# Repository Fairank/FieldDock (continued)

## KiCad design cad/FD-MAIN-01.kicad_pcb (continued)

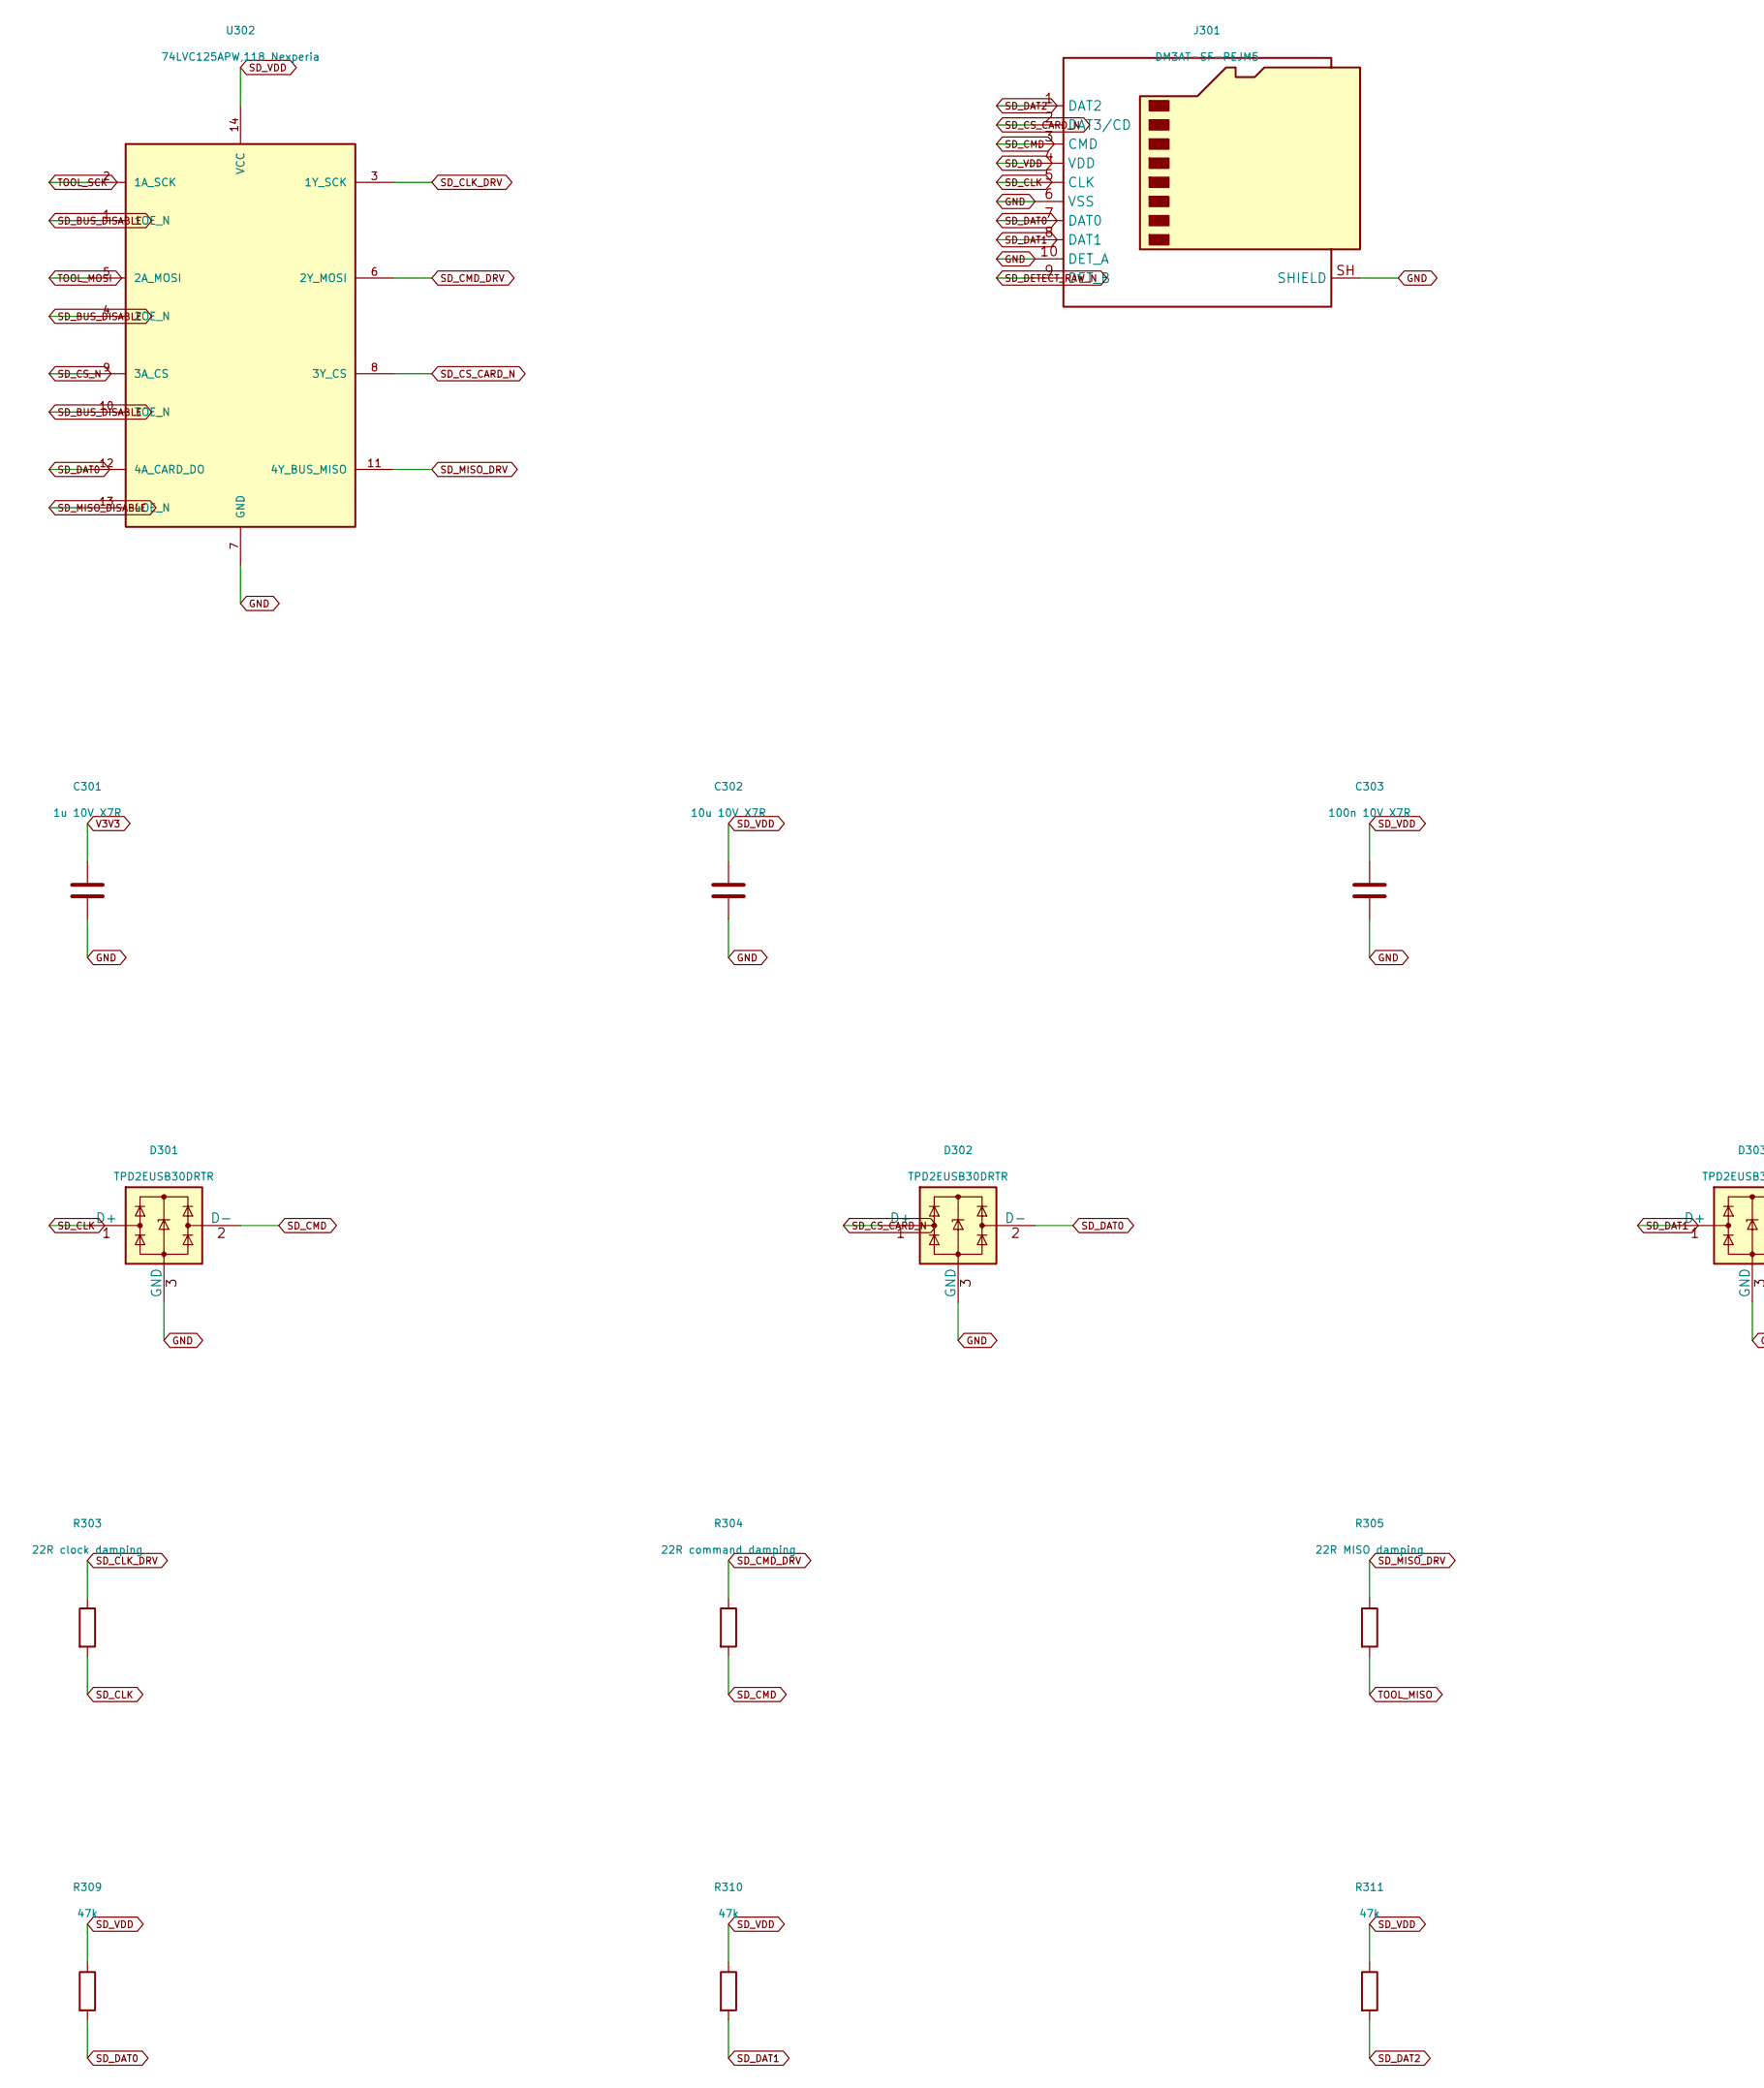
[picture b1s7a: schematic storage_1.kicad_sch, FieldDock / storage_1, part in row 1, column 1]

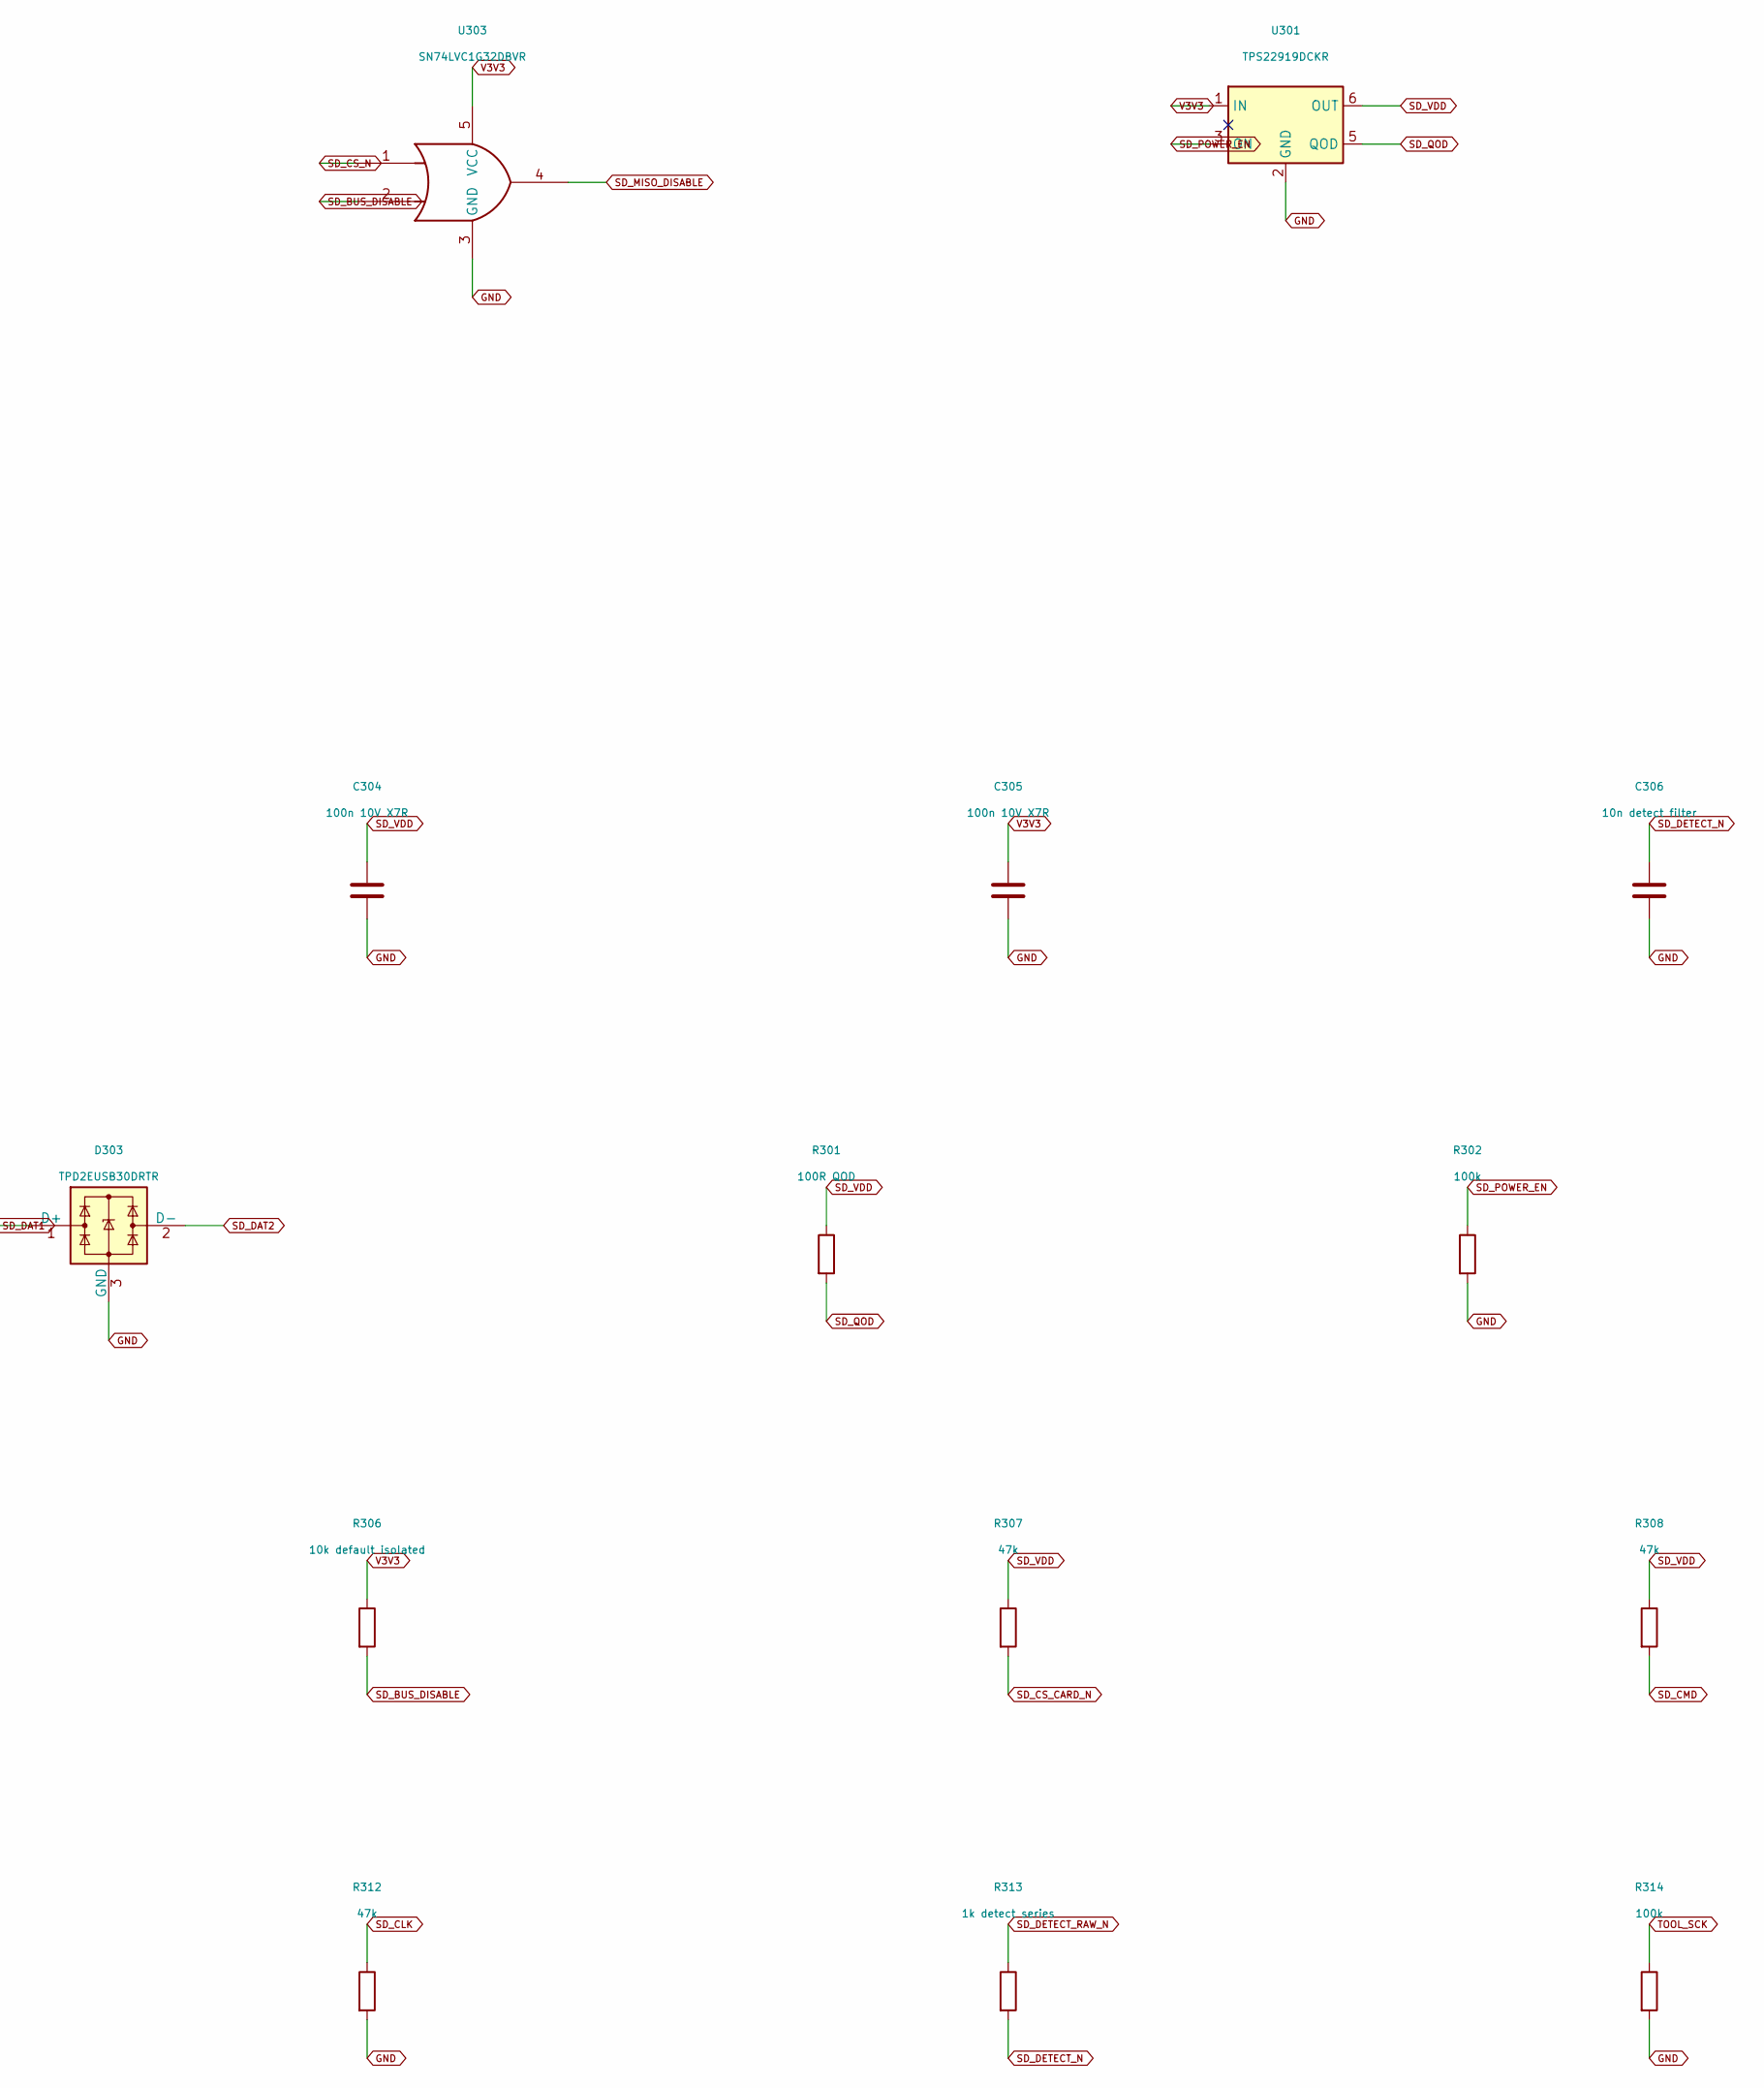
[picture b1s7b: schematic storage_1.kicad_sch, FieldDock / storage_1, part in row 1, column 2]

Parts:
C301: 1u 10V X7R; C_0603_1608Metric
C302: 10u 10V X7R; C_0805_2012Metric
C303, C304, C305: 100n 10V X7R; C_0603_1608Metric
C306: 10n detect filter; C_0603_1608Metric
D301, D302, D303: TPD2EUSB30DRTR; Texas_DRT-3
J301: DM3AT-SF-PEJM5; microSD_HC_Hirose_DM3AT-SF-PEJM5
R301: 100R QOD; R_0603_1608Metric
R302, R314: 100k; R_0603_1608Metric
R303: 22R clock damping; R_0603_1608Metric
R304: 22R command damping; R_0603_1608Metric
R305: 22R MISO damping; R_0603_1608Metric
R306: 10k default isolated; R_0603_1608Metric
R307, R308, R309, R310, R311, R312: 47k; R_0603_1608Metric
R313: 1k detect series; R_0603_1608Metric
U301: TPS22919DCKR; SOT-363_SC-70-6
U302: 74LVC125APW,118 Nexperia; TSSOP-14_4.4x5mm_P0.65mm
U303: SN74LVC1G32DBVR; SOT-23-5

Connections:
GND: C301.2, C302.2, C303.2, C304.2, C305.2, C306.2, D301.3 (GND), D302.3 (GND), D303.3 (GND), J301.6 (VSS), J301.10 (DET_A), J301.SH (SHIELD), R302.2, R312.2, R314.2, U301.2 (GND), U302.7 (GND), U303.3 (GND); also elsewhere on the board
SD_BUS_DISABLE: R306.2, U302.1 (1OE_N), U302.4 (2OE_N), U302.10 (3OE_N), U303.2; also elsewhere on the board
SD_CLK: D301.1 (D+), J301.5 (CLK), R303.2, R312.1
SD_CLK_DRV: R303.1, U302.3 (1Y_SCK)
SD_CMD: D301.2 (D-), J301.3 (CMD), R304.2, R308.2
SD_CMD_DRV: R304.1, U302.6 (2Y_MOSI)
SD_CS_CARD_N: D302.1 (D+), J301.2 (DAT3/CD), R307.2, U302.8 (3Y_CS)
SD_CS_N: U302.9 (3A_CS), U303.1; also elsewhere on the board
SD_DAT0: D302.2 (D-), J301.7 (DAT0), R309.2, U302.12 (4A_CARD_DO)
SD_DAT1: D303.1 (D+), J301.8 (DAT1), R310.2
SD_DAT2: D303.2 (D-), J301.1 (DAT2), R311.2
SD_DETECT_N: C306.1, R313.2; also elsewhere on the board
SD_DETECT_RAW_N: J301.9 (DET_B), R313.1
SD_MISO_DISABLE: U302.13 (4OE_N), U303.4; also elsewhere on the board
SD_MISO_DRV: R305.1, U302.11 (4Y_BUS_MISO)
SD_POWER_EN: R302.1, U301.3 (ON); also elsewhere on the board
SD_QOD: R301.2, U301.5 (QOD)
SD_VDD: C302.1, C303.1, C304.1, J301.4 (VDD), R301.1, R307.1, R308.1, R309.1, R310.1, R311.1, U301.6 (OUT), U302.14 (VCC)
TOOL_MISO: R305.2; also elsewhere on the board
TOOL_MOSI: U302.5 (2A_MOSI); also elsewhere on the board
TOOL_SCK: R314.1, U302.2 (1A_SCK); also elsewhere on the board
V3V3: C301.1, C305.1, R306.1, U301.1 (IN), U303.5 (VCC); also elsewhere on the board

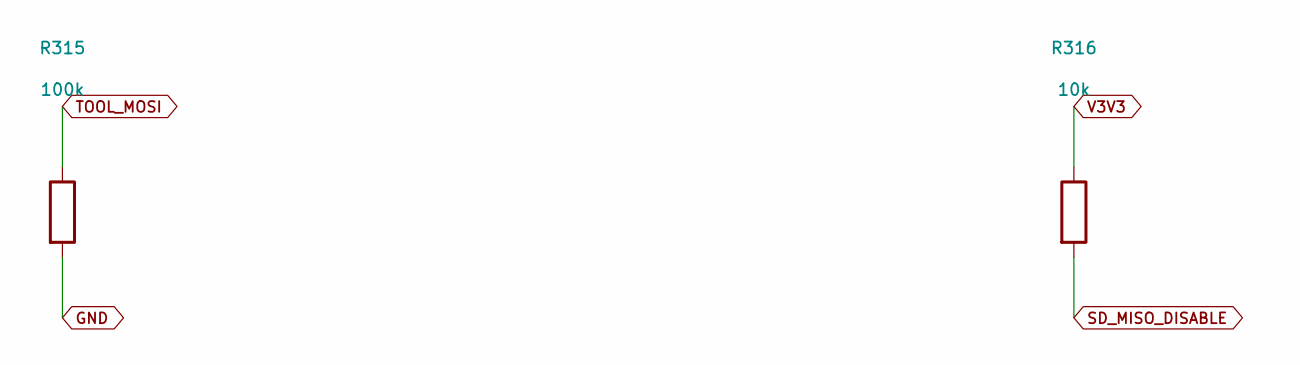
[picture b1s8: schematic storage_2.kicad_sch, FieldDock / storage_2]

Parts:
R315: 100k; R_0603_1608Metric
R316: 10k; R_0603_1608Metric

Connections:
GND: R315.2; also elsewhere on the board
SD_MISO_DISABLE: R316.2; also elsewhere on the board
TOOL_MOSI: R315.1; also elsewhere on the board
V3V3: R316.1; also elsewhere on the board

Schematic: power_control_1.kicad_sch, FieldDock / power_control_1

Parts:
C180: 1u 10V X7R; C_0603_1608Metric
C181: 10u 10V X7R; C_0805_2012Metric
C190, C194: 1n 50V C0G; C_0603_1608Metric
C191, C192, C195, C196, C197: 100n 10V X7R; C_0603_1608Metric
R180: 34.0k 1%; R_0402_1005Metric
R181, R197, R198, R199: 100k 1%; R_0402_1005Metric
R182: 1k 1%; R_0402_1005Metric
R190, R194: 324k 1%; R_0402_1005Metric
R191, R195: 33.2k 1%; R_0402_1005Metric
R192, R193, R196: 10k 1%; R_0402_1005Metric
U190: TPS3700DDCR; SOT-23-6
U191: SN74LVC1G04DBVR; SOT-23-5
U192, U193, U194: SN74LVC1G08DBVR; SOT-23-5
U195: TPS2553DBVR; SOT-23-6

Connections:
AUX_5V_PROTECTED: C180.1, U195.1 (IN); also elsewhere on the board
AUX_PROBE_ALLOWED: U192.4, U194.1
AUX_PROBE_BUDGET_OK: R197.1, U192.2; also elsewhere on the board
AUX_VBUS_RAW: R194.1; also elsewhere on the board
AUX_VGOOD_N: R193.2, U190.6 (OUTB), U191.2
AUX_VSENSE: C194.1, R194.2, R195.1, U190.4 (INB_N)
EXT_FAULT_N: R181.2, U195.4 (FAULT_N)
EXT_GOOD: U191.4, U192.1; also elsewhere on the board
EXT_ILIM: R180.1, U195.5 (ILIM)
EXT_LOAD_ENABLE: R199.1, U194.4, U195.3 (EN); also elsewhere on the board
EXT_PROBE5: C181.1, R182.1, U195.6 (OUT); also elsewhere on the board
EXT_REQUEST: R198.1, U193.2; also elsewhere on the board
GND: C180.2, C181.2, C190.2, C191.2, C192.2, C194.2, C195.2, C196.2, C197.2, R180.2, R182.2, R191.2, R195.2, R197.2, R198.2, R199.2, U190.2 (GND), U191.3 (GND), U192.3 (GND), U193.3 (GND), U194.3 (GND), U195.2 (GND); also elsewhere on the board
MGMT_IRQ_N: R196.2; also elsewhere on the board
PHONE_ATTACHED: R192.2, U190.1 (OUTA); also elsewhere on the board
PHONE_VBUS_RAW: R190.1; also elsewhere on the board
PHONE_VSENSE: C190.1, R190.2, R191.1, U190.3 (INA_P)
PROBE_REQUEST_ALLOWED: U193.4, U194.2
TOOLS_ENABLE: U193.1; also elsewhere on the board
V3V3: C191.1, C192.1, C195.1, C196.1, C197.1, R181.1, R192.1, R193.1, R196.1, U190.5 (VDD), U191.5 (VCC), U192.5 (VCC), U193.5 (VCC), U194.5 (VCC); also elsewhere on the board

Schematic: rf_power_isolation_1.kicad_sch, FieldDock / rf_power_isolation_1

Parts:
C400: 1u 10V X7R; C_0603_1608Metric
C401: 4.7u 10V X7R; C_0603_1608Metric
C402, C403, C404: 100n 10V X7R; C_0402_1005Metric
R400: 100R; R_0402_1005Metric
R401, R403, R406, R407, R408, R409, R410: 100k; R_0402_1005Metric
R402: 10k; R_0402_1005Metric
R404, R405: 47k; R_0402_1005Metric
U400: TPS22919DCKR; SOT-363_SC-70-6
U401: SN74LVC1G08DBVR; SOT-23-5
U402: SN74LVC1G04DBVR; SOT-23-5
U403: SN74CB3T3245PWR; TSSOP-20_4.4x6.5mm_P0.65mm

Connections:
GND: C400.2, C401.2, C402.2, C403.2, C404.2, R401.2, R403.2, R406.2, R407.2, R408.2, R409.2, R410.2, U400.2 (GND), U401.3 (GND), U402.3 (GND), U403.10 (GND); also elsewhere on the board
NFC_CS_N: U403.6 (A5); also elsewhere on the board
NFC_IRQ: R409.1, U403.8 (A7); also elsewhere on the board
RF_NFC_CS_N: R405.2, U403.14 (B5); also elsewhere on the board
RF_NFC_IRQ: U403.12 (B7); also elsewhere on the board
RF_QOD: R400.2, U400.5 (QOD)
RF_SUB_CS_N: R404.2, U403.15 (B4); also elsewhere on the board
RF_SUB_GDO0: U403.13 (B6); also elsewhere on the board
RF_SUB_RF_SELECT: R408.1, U403.11 (B8); also elsewhere on the board
RF_TOOL_MISO: U403.16 (B3); also elsewhere on the board
RF_TOOL_MOSI: R407.1, U403.17 (B2); also elsewhere on the board
RF_TOOL_SCK: R406.1, U403.18 (B1); also elsewhere on the board
SUB_CS_N: U403.5 (A4); also elsewhere on the board
SUB_GDO0: R410.1, U403.7 (A6); also elsewhere on the board
SUB_RF_SELECT: U403.9 (A8); also elsewhere on the board
TOOLS_BUS_DISABLE: R402.2, U402.4, U403.19 (OE_N); also elsewhere on the board
TOOLS_ENABLE: U400.3 (ON), U401.1; also elsewhere on the board
TOOLS_IO_ARM: R401.1, U401.2; also elsewhere on the board
TOOLS_IO_ENABLED: R403.1, U401.4, U402.2; also elsewhere on the board
TOOL_MISO: U403.4 (A3); also elsewhere on the board
TOOL_MOSI: U403.3 (A2); also elsewhere on the board
TOOL_SCK: U403.2 (A1); also elsewhere on the board
V3V3: C400.1, C402.1, C403.1, C404.1, R402.1, U400.1 (IN), U401.5 (VCC), U402.5 (VCC), U403.20 (VCC); also elsewhere on the board
V3V3_RF: C401.1, R400.1, R404.1, R405.1, U400.6 (OUT); also elsewhere on the board

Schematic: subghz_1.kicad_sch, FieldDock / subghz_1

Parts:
C430, C431: 9p C0G 50V initial CL trim; C_0402_1005Metric
C432, C433, C434, C435, C436, C437, C438: 100n 10V X7R; C_0402_1005Metric
C439: 2.2u 10V X7R; C_0603_1608Metric
C440, C441: 100p C0G 50V; C_0402_1005Metric
C442: 1.2p C0G 0.1p 50V; C_0402_1005Metric
C443, C444, C445: DNP C0G matching trim; C_0402_1005Metric
C446, C447: 10n 10V X7R; C_0402_1005Metric
C450, C451: 12p C0G 2% 50V; C_0402_1005Metric
C452, C453: 8.2p C0G 2% 50V; C_0402_1005Metric
C454, C455: 4.3p C0G 2% 50V; C_0402_1005Metric
J430: U.FL-R-SMT-1(10) / 50R antenna; U.FL_Hirose_U.FL-R-SMT-1_Vertical
U430: CC1101RGPT; Texas_RGP0020H_VQFN-20-1EP_4x4mm_P0.5mm_EP2.4x2.4mm
U431, U432: BGS13S4N9E6327XTSA1; Infineon_TSNP9_1.1x1.1_P0.4

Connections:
GND: C430.2, C431.2, C432.2, C433.2, C434.2, C435.2, C436.2, C437.2, C438.2, C439.2, C442.2, C443.2, C444.2, C445.2, C446.2, C447.2, C450.2, C451.2, C452.2, C453.2, C454.2, C455.2, J430.2 (Ext), U430.16 (GND1), U430.18 (DGUARD), U430.19 (GND2), U430.21 (EP_GND), U431.6 (DGND), U431.9 (GND), U432.6 (DGND), U432.9 (GND); also elsewhere on the board
RF_SUB_CS_N: U430.7 (CS_N); also elsewhere on the board
RF_SUB_GDO0: U430.6 (GDO0); also elsewhere on the board
RF_SUB_RF_SELECT: U431.1 (V1), U432.1 (V1); also elsewhere on the board
RF_TOOL_MISO: U430.2 (SO_GDO1); also elsewhere on the board
RF_TOOL_MOSI: U430.20 (SI); also elsewhere on the board
RF_TOOL_SCK: U430.1 (SCLK); also elsewhere on the board
SUB_ANT: J430.1 (In); also elsewhere on the board
SUB_BAL_A: C440.2; also elsewhere on the board
SUB_BAL_B: C441.2; also elsewhere on the board
SUB_DCOUPL: C432.1, U430.5 (DCOUPL)
SUB_FILTER_IN: C445.1, U431.4 (RFIN); also elsewhere on the board
SUB_FILTER_OUT: U432.4 (RFIN); also elsewhere on the board
SUB_F_IN_315: U431.3 (RF1); also elsewhere on the board
SUB_F_IN_433: U431.5 (RF2); also elsewhere on the board
SUB_F_IN_900: U431.2 (RF3); also elsewhere on the board
SUB_F_M1_315: C450.1; also elsewhere on the board
SUB_F_M1_433: C452.1; also elsewhere on the board
SUB_F_M1_900: C454.1; also elsewhere on the board
SUB_F_M2_315: C451.1; also elsewhere on the board
SUB_F_M2_433: C453.1; also elsewhere on the board
SUB_F_M2_900: C455.1; also elsewhere on the board
SUB_F_OUT_315: U432.3 (RF1); also elsewhere on the board
SUB_F_OUT_433: U432.5 (RF2); also elsewhere on the board
SUB_F_OUT_900: U432.2 (RF3); also elsewhere on the board
SUB_MATCH: C442.1; also elsewhere on the board
SUB_RBIAS: U430.17 (RBIAS); also elsewhere on the board
SUB_RFN: C440.1, C444.1, U430.13 (RF_N)
SUB_RFP: C441.1, C443.1, U430.12 (RF_P)
SUB_SWITCH_V2: U430.3 (GDO2), U431.8 (V2), U432.8 (V2); also elsewhere on the board
SUB_X1: C430.1, U430.8 (XOSC_Q1); also elsewhere on the board
SUB_X2: C431.1, U430.10 (XOSC_Q2); also elsewhere on the board
V3V3_RF: C433.1, C434.1, C435.1, C436.1, C437.1, C438.1, C439.1, C446.1, C447.1, U430.4 (DVDD), U430.9 (AVDD1), U430.11 (AVDD2), U430.14 (AVDD3), U430.15 (AVDD4), U431.7 (VDD), U432.7 (VDD); also elsewhere on the board

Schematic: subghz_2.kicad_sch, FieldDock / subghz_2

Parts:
L430: 3.3nH 0.2nH RF; L_0402_1005Metric
L431: 6.8nH 0.2nH RF; L_0402_1005Metric
L440, L442: 12nH 5% RF; L_0402_1005Metric
L441: 39nH 5% RF; L_0402_1005Metric
L443, L445: 8.2nH 5% RF; L_0402_1005Metric
L444: 27nH 5% RF; L_0402_1005Metric
L446, L448: 4.3nH 5% RF; L_0402_1005Metric
L447: 13nH 5% RF; L_0402_1005Metric
R430: 56k 1%; R_0402_1005Metric
R431: 100k; R_0402_1005Metric
R432: 0R antenna matching link; R_0402_1005Metric
T430: B0310J50100AHF; TTM_B0310J50100AHF
Y430: XRCGB26M000F3M00R0 26MHz CL6pF; Murata_XRCGB_2016

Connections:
GND: R430.2, R431.2, T430.2 (GND); also elsewhere on the board
SUB_ANT: R432.2; also elsewhere on the board
SUB_BAL_A: T430.3 (BAL_100R_A); also elsewhere on the board
SUB_BAL_B: T430.4 (BAL_100R_B); also elsewhere on the board
SUB_FILTER_IN: L431.2; also elsewhere on the board
SUB_FILTER_OUT: R432.1; also elsewhere on the board
SUB_F_IN_315: L440.1; also elsewhere on the board
SUB_F_IN_433: L443.1; also elsewhere on the board
SUB_F_IN_900: L446.1; also elsewhere on the board
SUB_F_M1_315: L440.2, L441.1; also elsewhere on the board
SUB_F_M1_433: L443.2, L444.1; also elsewhere on the board
SUB_F_M1_900: L446.2, L447.1; also elsewhere on the board
SUB_F_M2_315: L441.2, L442.1; also elsewhere on the board
SUB_F_M2_433: L444.2, L445.1; also elsewhere on the board
SUB_F_M2_900: L447.2, L448.1; also elsewhere on the board
SUB_F_OUT_315: L442.2; also elsewhere on the board
SUB_F_OUT_433: L445.2; also elsewhere on the board
SUB_F_OUT_900: L448.2; also elsewhere on the board
SUB_MATCH: L430.2, L431.1; also elsewhere on the board
SUB_RBIAS: R430.1; also elsewhere on the board
SUB_SWITCH_V2: R431.1; also elsewhere on the board
SUB_UNBAL: L430.1, T430.1 (UNBAL_50R)
SUB_X1: Y430.1 (XTAL_1); also elsewhere on the board
SUB_X2: Y430.3 (XTAL_3); also elsewhere on the board

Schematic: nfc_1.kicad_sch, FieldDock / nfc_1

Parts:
C500, C501: 6p C0G 50V; C_0402_1005Metric
C502, C504, C506, C508, C510, C513: 10n 10V X7R; C_0402_1005Metric
C503, C505, C507, C509, C511: 2.2u 10V X7R; C_0603_1608Metric
C512: 1u 10V X7R; C_0603_1608Metric
C520, C525: 680p C0G 50V; C_0603_1608Metric
C521, C526: 100p C0G 100V; C_0603_1608Metric
C522, C527: 62p C0G 100V; C_0603_1608Metric
C523, C528: 10p C0G 100V; C_0603_1608Metric
C524, C529: 100p C0G 50V; C_0603_1608Metric
C530, C531: DNP C0G trim; C_0603_1608Metric
J500: NFC antenna 1.37uH nominal / soldered twisted pair; Antenna_2Pad_2mm
L500: 270nH 5% RF wirewound; L_0603_1608Metric
U500: ST25R3916-AQWT; ST_VFQFPN32_5x5_EP3.5

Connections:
GND: C500.2, C501.2, C502.2, C503.2, C504.2, C505.2, C506.2, C507.2, C508.2, C509.2, C510.2, C511.2, C512.2, C513.2, C520.2, C522.2, C524.2, C525.2, C527.2, C529.2, U500.6 (GND_D), U500.12 (GND_DR1), U500.16 (GND_DR2), U500.20 (I2C_EN), U500.21 (VSS), U500.26 (GND_A), U500.33 (EP_GND); also elsewhere on the board
NFC_AGDC: C512.1, C513.1, U500.24 (AGDC)
NFC_ANT_N: C526.2, C527.1, C528.1, C531.2; also elsewhere on the board
NFC_ANT_P: C521.2, C522.1, C523.1, C530.2; also elsewhere on the board
NFC_COIL_N: J500.2; also elsewhere on the board
NFC_COIL_P: J500.1; also elsewhere on the board
NFC_FILTER_N: C525.1, C526.1, C531.1; also elsewhere on the board
NFC_FILTER_P: C520.1, C521.1, C530.1, L500.2
NFC_RFI1: C523.2, C524.1, U500.22 (RFI1)
NFC_RFI2: C528.2, C529.1, U500.23 (RFI2)
NFC_RFO1: L500.1, U500.13 (RFO1)
NFC_RFO2: U500.15 (RFO2); also elsewhere on the board
NFC_VDD_A: C506.1, C507.1, U500.7 (VDD_A)
NFC_VDD_AM: C510.1, C511.1, U500.11 (VDD_AM)
NFC_VDD_D: C504.1, C505.1, U500.3 (VDD_D)
NFC_VDD_RF: C508.1, C509.1, U500.9 (VDD_RF), U500.14 (VDD_DR)
NFC_XTI: C501.1, U500.5 (XTI); also elsewhere on the board
NFC_XTO: C500.1, U500.4 (XTO); also elsewhere on the board
RF_NFC_CS_N: U500.29 (BSS_N); also elsewhere on the board
RF_NFC_IRQ: U500.27 (IRQ); also elsewhere on the board
RF_TOOL_MISO: U500.32 (MISO); also elsewhere on the board
RF_TOOL_MOSI: U500.31 (MOSI); also elsewhere on the board
RF_TOOL_SCK: U500.30 (SCLK); also elsewhere on the board
V3V3_RF: C502.1, C503.1, U500.1 (VDD_IO), U500.8 (VDD), U500.10 (VDD_TX); also elsewhere on the board

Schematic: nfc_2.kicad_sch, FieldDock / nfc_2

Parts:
L501: 270nH 5% RF wirewound; L_0603_1608Metric
R500, R501: 0R antenna tuning link; R_0603_1608Metric
Y500: XRCGB27M120F3M00R0 27.12MHz CL6pF; Murata_XRCGB_2016

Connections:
NFC_ANT_N: R501.1; also elsewhere on the board
NFC_ANT_P: R500.1; also elsewhere on the board
NFC_COIL_N: R501.2; also elsewhere on the board
NFC_COIL_P: R500.2; also elsewhere on the board
NFC_FILTER_N: L501.2; also elsewhere on the board
NFC_RFO2: L501.1; also elsewhere on the board
NFC_XTI: Y500.3 (XTAL_3); also elsewhere on the board
NFC_XTO: Y500.1 (XTAL_1); also elsewhere on the board

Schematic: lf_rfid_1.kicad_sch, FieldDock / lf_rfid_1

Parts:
C600, C610, C611: 1u 10V X7R; C_0603_1608Metric
C601: 4.7u 10V X7R; C_0603_1608Metric
C602, C603, C609, C612, C613, C625: 100n 10V X7R; C_0402_1005Metric
C604: 3.3n C0G 100V; C_0805_2012Metric
C605: DNP C0G 100V trim; C_0805_2012Metric
C606: 10n X7R 100V; C_0603_1608Metric
C607: 1n C0G 100V; C_0603_1608Metric
C608: 220n X7R 100V; C_0805_2012Metric
C620, C622: 4.7n C0G 50V; C_0402_1005Metric
C621, C623, C624: 100p C0G 50V; C_0402_1005Metric
D600: 1N4148W-7-F; D_SOD-123
D601: MM3Z33VT1G 33V; D_SOD-323
D602: BAT54S,215; SOT-23
J600: LF coil ~500uH / soldered twisted pair; Antenna_2Pad_2mm
U600, U601, U603: SN74LVC1G08DBVR; SOT-23-5
U602: TPS22919DCKR; SOT-363_SC-70-6
U604, U605: LMV358AIDGKR; VSSOP-8_3x3mm_P0.65mm
U606: LMV331IDCKR; SOT-353_SC-70-5

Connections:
CORE5: C600.1, U602.1 (IN); also elsewhere on the board
GND: C600.2, C601.2, C602.2, C603.2, C604.2, C605.2, C606.2, C607.2, C609.2, C610.2, C611.2, C612.2, C613.2, C620.2, C622.2, C624.2, C625.2, D601.2 (A), D602.1 (A), U600.3 (GND), U601.3 (GND), U602.2 (GND), U603.3 (GND), U604.4 (GND), U605.4 (GND), U606.2 (GND), U606.3 (IN_N); also elsewhere on the board
LF5: C601.1, U602.6 (OUT); also elsewhere on the board
LF_AC: C608.2, D602.3 (COM), U604.3 (IN_A_P); also elsewhere on the board
LF_ANALOG: C624.1; also elsewhere on the board
LF_AR1: J600.1; also elsewhere on the board
LF_AR2: C604.1, C605.1, D600.2 (A), J600.2; also elsewhere on the board
LF_AVDD: C610.1, C612.1, C613.1, C625.1, D602.2 (K), U604.8 (VCC), U605.8 (VCC), U606.5 (VCC); also elsewhere on the board
LF_CARRIER: U601.1; also elsewhere on the board
LF_CARRIER_SENSE: U606.1 (IN_P); also elsewhere on the board
LF_DRIVE_GATED: U601.4; also elsewhere on the board
LF_EDGE: U606.4 (OUT); also elsewhere on the board
LF_ENV: C607.1, C608.1; also elsewhere on the board
LF_F1_NEG: C621.1, U605.2 (IN_A_N); also elsewhere on the board
LF_F1_NODE: C620.1; also elsewhere on the board
LF_F2_NEG: C623.1, U605.6 (IN_B_N); also elsewhere on the board
LF_F2_NODE: C622.1; also elsewhere on the board
LF_FB1: U604.2 (IN_A_N); also elsewhere on the board
LF_FILTER1: C621.2, U605.1 (OUT_A); also elsewhere on the board
LF_FILTER2: C623.2, U605.7 (OUT_B); also elsewhere on the board
LF_GAIN1: U604.1 (OUT_A); also elsewhere on the board
LF_LOAD: U603.1; also elsewhere on the board
LF_LOAD_GATED: U603.4; also elsewhere on the board
LF_MID: U604.6 (IN_B_N), U604.7 (OUT_B), U605.3 (IN_A_P), U605.5 (IN_B_P); also elsewhere on the board
LF_MID_DIV: C611.1, U604.5 (IN_B_P); also elsewhere on the board
LF_POWER_ON: U600.4, U601.2, U602.3 (ON); also elsewhere on the board
LF_QOD: U602.5 (QOD); also elsewhere on the board
LF_RECT: C606.1, D600.1 (K), D601.1 (K); also elsewhere on the board
LF_REQUEST: U600.2; also elsewhere on the board
TOOLS_IO_ENABLED: U600.1, U603.2; also elsewhere on the board
V3V3: C602.1, C603.1, C609.1, U600.5 (VCC), U601.5 (VCC), U603.5 (VCC); also elsewhere on the board

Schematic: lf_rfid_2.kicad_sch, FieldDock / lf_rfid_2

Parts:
D603: BAT54S,215; SOT-23
Q600: DMP2004K-7; SOT-23
Q601, Q602: DMN2004K-7; SOT-23
Q603: DMN5L06TK-7; SOT-523
R600: 100R; R_0402_1005Metric
R601, R602, R611: 100k; R_0402_1005Metric
R603, R604: 4.7R 1% 0.25W; R_0805_2012Metric
R605: 510R 1%; R_0402_1005Metric
R606: 51R; R_0402_1005Metric
R607, R629: 10k; R_0402_1005Metric
R608, R628: 330k 1%; R_0402_1005Metric
R609: 5.1k; R_0402_1005Metric
R610: 440R; R_0402_1005Metric
R612: 330R 0.25W; R_0805_2012Metric
R613: 10R; R_0402_1005Metric
R614, R615, R626: 33k 1%; R_0402_1005Metric
R616: 1M 1%; R_0402_1005Metric
R617, R620, R621, R623, R624: 1k 1%; R_0402_1005Metric
R618: 4.7k 1%; R_0402_1005Metric
R622, R625: 10k 1%; R_0402_1005Metric
R627: 20k 1%; R_0402_1005Metric

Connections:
GND: D603.1 (A), Q601.2 (S), Q602.2 (S), Q603.2 (S), R601.2, R602.2, R607.2, R608.2, R611.2, R615.2, R627.2; also elsewhere on the board
LF5: Q600.2 (S), R600.1, R605.1; also elsewhere on the board
LF_AC: R616.1; also elsewhere on the board
LF_ANALOG: R626.2, R627.1; also elsewhere on the board
LF_AR1: R603.2, R604.2; also elsewhere on the board
LF_AR2: R628.1; also elsewhere on the board
LF_AVDD: D603.2 (K), R613.2, R614.1; also elsewhere on the board
LF_CARRIER_SENSE: D603.3 (COM), R628.2; also elsewhere on the board
LF_DRIVER_GATE: Q600.1 (G), Q601.1 (G), Q602.3 (D), R605.2
LF_DRIVE_GATED: R606.1; also elsewhere on the board
LF_EDGE: R629.2; also elsewhere on the board
LF_ENV: R609.2; also elsewhere on the board
LF_F1_NEG: R621.2; also elsewhere on the board
LF_F1_NODE: R620.2, R621.1, R622.1; also elsewhere on the board
LF_F2_NEG: R624.2; also elsewhere on the board
LF_F2_NODE: R623.2, R624.1, R625.1; also elsewhere on the board
LF_FB1: R617.1, R618.1; also elsewhere on the board
LF_FILTER1: R622.2, R623.1; also elsewhere on the board
LF_FILTER2: R625.2, R626.1; also elsewhere on the board
LF_GAIN1: R618.2, R620.1; also elsewhere on the board
LF_LEVEL_GATE: Q602.1 (G), R606.2, R607.1
LF_LOAD_DRAIN: Q603.3 (D), R612.2
LF_LOAD_GATE: Q603.1 (G), R610.2, R611.1
LF_LOAD_GATED: R610.1; also elsewhere on the board
LF_MID: R616.2, R617.2; also elsewhere on the board
LF_MID_DIV: R614.2, R615.1; also elsewhere on the board
LF_N_DRAIN: Q601.3 (D), R604.1
LF_POWER_ON: R602.1; also elsewhere on the board
LF_P_DRAIN: Q600.3 (D), R603.1
LF_QOD: R600.2; also elsewhere on the board
LF_RECT: R608.1, R609.1, R612.1; also elsewhere on the board
LF_REQUEST: R601.1; also elsewhere on the board
V3V3: R629.1; also elsewhere on the board
V3V3_RF: R613.1; also elsewhere on the board

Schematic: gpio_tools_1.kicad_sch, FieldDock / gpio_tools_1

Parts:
C700, C701: 100n 10V X7R; C_0402_1005Metric
C702, C703: 1u 10V X7R; C_0603_1608Metric
D700, D701, D702, D703, D704, D705, D706: TPD2EUSB30DRTR; Texas_DRT-3
J700: 2x8 2.54mm GPIO 3.3V / 5V-tolerant inputs; PinHeader_2x08_P2.54mm_Vertical_SMD
R700, R701, R702, R703, R704, R705, R706, R707, R708, R709: 51R; R_0402_1005Metric
U700, U701: SN74CB3T3245PWR; TSSOP-20_4.4x6.5mm_P0.65mm
U702: TPS2553DBVR; SOT-23-6

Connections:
AUX_CAPTURE: U701.8 (A7); also elsewhere on the board
EXT_AUX_CAPTURE: U701.12 (B7); also elsewhere on the board
EXT_IBTN_EDGE: U701.13 (B6); also elsewhere on the board
EXT_IR_EDGE: U701.11 (B8); also elsewhere on the board
EXT_TARGET_CS_N: R703.1, U700.15 (B4)
EXT_TARGET_IO0: R708.1, U701.18 (B1)
EXT_TARGET_IO1: R709.1, U701.17 (B2)
EXT_TARGET_IO2: U701.16 (B3); also elsewhere on the board
EXT_TARGET_IO3: U701.15 (B4); also elsewhere on the board
EXT_TARGET_IO4: U701.14 (B5); also elsewhere on the board
EXT_TARGET_MISO: R701.1, U700.17 (B2)
EXT_TARGET_MOSI: R702.1, U700.16 (B3)
EXT_TARGET_RX: R705.1, U700.13 (B6)
EXT_TARGET_SCK: R700.1, U700.18 (B1)
EXT_TARGET_SCL: R706.1, U700.12 (B7)
EXT_TARGET_SDA: R707.1, U700.11 (B8)
EXT_TARGET_TX: R704.1, U700.14 (B5)
GND: C700.2, C701.2, C702.2, C703.2, D700.3 (GND), D701.3 (GND), D702.3 (GND), D703.3 (GND), D704.3 (GND), D705.3 (GND), D706.3 (GND), J700.1, J700.16, U700.10 (GND), U701.10 (GND), U702.2 (GND); also elsewhere on the board
HDR_GND_GUARD: D706.2 (D-); also elsewhere on the board
HDR_TARGET_CS_N: D701.2 (D-), J700.6, R703.2
HDR_TARGET_IO0: D704.1 (D+), J700.11, R708.2
HDR_TARGET_IO1: D704.2 (D-), J700.12, R709.2
HDR_TARGET_IO2: D705.1 (D+), J700.13; also elsewhere on the board
HDR_TARGET_IO3: D705.2 (D-), J700.14; also elsewhere on the board
HDR_TARGET_IO4: D706.1 (D+), J700.15; also elsewhere on the board
HDR_TARGET_MISO: D700.2 (D-), J700.4, R701.2
HDR_TARGET_MOSI: D701.1 (D+), J700.5, R702.2
HDR_TARGET_RX: D702.2 (D-), J700.8, R705.2
HDR_TARGET_SCK: D700.1 (D+), J700.3, R700.2
HDR_TARGET_SCL: D703.1 (D+), J700.9, R706.2; also elsewhere on the board
HDR_TARGET_SDA: D703.2 (D-), J700.10, R707.2; also elsewhere on the board
HDR_TARGET_TX: D702.1 (D+), J700.7, R704.2
IBTN_EDGE: U701.7 (A6); also elsewhere on the board
IR_EDGE: U701.9 (A8); also elsewhere on the board
TARGET_CS_N: U700.5 (A4); also elsewhere on the board
TARGET_ILIM: U702.5 (ILIM); also elsewhere on the board
TARGET_IO0: U701.2 (A1); also elsewhere on the board
TARGET_IO1: U701.3 (A2); also elsewhere on the board
TARGET_IO2: U701.4 (A3); also elsewhere on the board
TARGET_IO3: U701.5 (A4); also elsewhere on the board
TARGET_IO4: U701.6 (A5); also elsewhere on the board
TARGET_MISO: U700.3 (A2); also elsewhere on the board
TARGET_MOSI: U700.4 (A3); also elsewhere on the board
TARGET_POWER_FAULT_N: U702.4 (FAULT_N); also elsewhere on the board
TARGET_RX: U700.7 (A6); also elsewhere on the board
TARGET_SCK: U700.2 (A1); also elsewhere on the board
TARGET_SCL: U700.8 (A7); also elsewhere on the board
TARGET_SDA: U700.9 (A8); also elsewhere on the board
TARGET_TX: U700.6 (A5); also elsewhere on the board
TOOLS_BUS_DISABLE: U700.19 (OE_N), U701.19 (OE_N); also elsewhere on the board
TOOLS_IO_ENABLED: U702.3 (EN); also elsewhere on the board
V3V3: C700.1, C701.1, C702.1, U700.20 (VCC), U701.20 (VCC), U702.1 (IN); also elsewhere on the board
V3V3_TARGET: C703.1, J700.2, U702.6 (OUT); also elsewhere on the board
